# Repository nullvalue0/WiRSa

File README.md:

# RetroDisks WiRSa v3 - WiFi RS232 Serial Modem Adapter

The WiRSa v3 is a WiFi-to-RS232 serial adapter designed for legacy computing systems. It allows vintage computers to connect to modern networks via WiFi, supporting telnet BBS connectivity, file transfers, and network gateway functionality.

## Kits & assembled units available for sale
If you prefer to save yourself some time, I have some units (fully assembled or kit) available for sale. I had quite a few PCB's made up and I am trying to keep these as cheap as possible. You can purchase on [SmallRun](https://smallrun.net/shop/retrodisks/wirsa-v3-wifi-rs232-serial-modem).

## Features

### Hardware

- **Processor:** ESP-WROOM-32D with WiFi and Bluetooth 4.2 BLE
- **Display:** 128x64 two-color OLED display for settings, commands, and real-time data
- **Serial Port:** Female DB9 (DE9) connector
- **Full RS232 Breakout:**
  - DSR/DTR (Data Set Ready / Data Terminal Ready)
  - RTS/CTS (Request to Send / Clear to Send)
  - DCD (Data Carrier Detect)
  - RI (Ring Indicator)
- **Storage:** Built-in micro SD card reader for file transfers and text playback
- **Power:**
  - USB-C power connector
  - Optional 2000mAh 3.7V Li-Po battery (~14 hours runtime)
- **Navigation:** Four physical buttons for menu navigation

### Operating Modes

1. **MODEM Mode** - Hayes-compatible AT command modem emulation for telnet/BBS connectivity
2. **Telnet Server** - Built-in telnet server allows for remote terminal access
3. **File Transfer** - Binary file transfer directly from SD card via XModem, YModem, and ZModem protocols
4. **Text Playback** - Display text files from SD card through the serial port
5. **PPP Gateway** - Point-to-Point Protocol gateway for TCP/IP networking
6. **SLIP Gateway** - Serial Line Internet Protocol gateway
7. **Utilities** - Diagnostics and troubleshooting tools including signal monitoring and loopback testing
8. **Config** - Settings for baud rate, serial configuration, display orientation, and more

### Software Features

- **AT Command Set** - Full Hayes-compatible modem commands
- **Web Interface** - Built-in web server for status monitoring, configuration and file management
- **Flow Control** - Hardware (RTS/CTS) and software (XON/XOFF) flow control
- **Speed Dial** - 10 programmable speed dial entries
- **PETSCII Translation** - Support for Commodore computers
- **Telnet Protocol** - Automatic Telnet IAC handling
- **OTA Updates** - Over-the-air firmware updates via HTTP

.jpg)

## Getting Started

### WiFi Configuration

1. Connect to your computer via serial port (default: 9600 baud, 8N1)
2. Enter your WiFi credentials using AT commands (2.4 GHz networks only):
   ```
   AT$SSID=YourNetworkName
   AT$PASS=YourPassword
   ```
3. Save settings: `AT&W`
4. Reboot or reconnect to apply

### Connecting to a BBS

Use the dial command with the host and port:
```
ATDT bbs.example.com:23
```

Or configure speed dial entries:
```
AT&Z0=bbs.example.com:23
ATDS0
```

### Useful AT Commands

| Command | Description |
|---------|-------------|
| `AT` | Test connection (returns OK) |
| `ATDT<host:port>` | Dial/connect to TCP host |
| `ATDS<0-9>` | Speed dial entry |
| `ATH` | Hang up connection |
| `ATA` | Answer incoming connection |
| `ATO` | Return online from command mode |
| `+++` | Escape to command mode (during connection) |
| `ATE0/1` | Echo off/on |
| `ATV0/1` | Verbose results off/on |
| `ATI` | Display network info |
| `AT&V` | View current settings |
| `AT&W` | Save settings to EEPROM |
| `ATZ` | Load settings from EEPROM |
| `AT&F` | Restore factory defaults |
| `AT&K<0/1/2>` | Flow control (0=none, 1=hardware, 2=software) |
| `ATNET<0/1>` | Telnet protocol handling off/on |
| `ATPET=<0/1>` | PETSCII translation off/on |
| `AT$SSID=` | Set WiFi SSID |
| `AT$PASS=` | Set WiFi password |
| `AT$SP=<port>` | Set listening port |
| `ATS0=<0/1>` | Auto-answer off/on |
| `ATFC` | Check for firmware updates |
| `ATFU` | Perform firmware update |
| `AT?` or `ATHELP` | Display help |
| `ATX` | Exit MODEM Mode, return to WiRSa main menu |

## File Transfers

The WiRSa supports binary file transfers directly from the SD card using industry-standard protocols:

- **XModem** - Basic 128-byte block transfer with checksum
- **YModem** - Batch file transfer with filename and size
- **ZModem** - Streaming protocol with CRC16/CRC32 and automatic resume

To transfer files:
1. Insert SD card with files
2. Select "File Transfer" from the main menu
3. Choose the transfer protocol
4. Select send or receive
5. Initiate the transfer from your terminal software

## SLIP / PPP Gateway Modes

The WiRSa provides full TCP/IP networking capabilities for vintage computers through two standard protocols: **SLIP** (Serial Line Internet Protocol) and **PPP** (Point-to-Point Protocol). These modes turn the WiRSa into a dial-up internet gateway, allowing retro systems to browse the web, use email clients, FTP, and access other network services.

### How It Works

Both modes operate as NAT (Network Address Translation) gateways:
1. The vintage computer connects via the serial port
2. The WiRSa performs NAT translation between the serial link and WiFi
3. Outbound traffic is routed to the internet via the ESP32's WiFi connection
4. The vintage computer appears to have full internet access

### SLIP Mode

SLIP is a simpler, older protocol with less overhead. It works well with:
- **DOS** with packet drivers (ETHERSLIP, SLIPPER, etc.)
- **Early Windows 3.x** with Trumpet Winsock
- **Classic Mac OS** with MacSLIP or InterSLIP
- **Linux** with `slattach`

**Default Configuration:**
- Gateway IP: 192.168.7.1 (WiRSa)
- Client IP: 192.168.7.2 (vintage computer)
- DNS: 8.8.8.8

### PPP Mode

PPP is more robust with built-in negotiation, authentication support, and error detection. It's the standard for:
- **Windows 95/98/ME** Dial-Up Networking
- **Windows 3.11** with Microsoft DUN
- **Mac OS 8/9** with PPP/Remote Access
- **Linux** with `pppd`

**Default Configuration:**
- Gateway IP: 192.168.8.1 (WiRSa)
- Client IP: 192.168.8.2 (assigned to client)
- Primary DNS: 8.8.8.8
- Secondary DNS: 8.8.4.4

### Entering SLIP/PPP Mode

**From the WiRSa Menu: (*if your host OS is expecting an "always on" connection*)**
1. Navigate to "PPP Gateway" or "SLIP Gateway" from the main menu
2. Select "Start Gateway"

**Using AT Dial Commands: (*must set the device to Modem Mode first*)**
```
ATDT SLIP      - Enter SLIP mode
ATDT 7547      - Enter SLIP mode (phone keypad for "SLIP")

ATDT PPP       - Enter PPP mode
ATDT 777       - Enter PPP mode (phone keypad for "PPP")
```

**Using AT Commands: (*must set the device to Modem Mode first*)**
```
AT$SLIP        - Enter SLIP mode directly
AT$PPP         - Enter PPP mode directly
```

### Port Forwarding

Port forwarding allows incoming connections from the internet to reach services running on your vintage computer. This is useful for:

- **Hosting a BBS** - Run a BBS on your vintage computer accessible from the internet
- **FTP Server** - Share files from your retro machine
- **Web Server** - Host a vintage web server (Windows 95 Personal Web Server, etc.)
- **Game Servers** - Host multiplayer games on classic systems
- **SSH/Telnet Access** - Remote into your vintage computer

**Configuring Port Forwards:**

From the menu:
1. Enter SLIP or PPP Gateway menu
2. Select "Port Forwards"
3. Choose "Add Forward"
4. Enter protocol (TCP/UDP), external port, internal IP, and internal port

Using AT commands:
```
AT$SLIPFWD=TCP,80,80      - Forward TCP port 80 to client port 80
AT$SLIPFWD=UDP,53,53      - Forward UDP port 53 (DNS)
AT$SLIPFWDDEL=0           - Remove forward at index 0

AT$PPPFWD=TCP,23,23       - Forward TCP port 23 (telnet)
AT$PPPFWD=TCP,21,21       - Forward TCP port 21 (FTP)
AT$PPPFWDDEL=0            - Remove forward at index 0
```

**Note:** Port forwards are shared between SLIP and PPP modes and persist across reboots.

### Setting Up SLIP Under DOS

**Requirements:**
- MS-DOS, DR-DOS, FreeDOS, etc
- A SLIP packet driver (ETHERSLIP, SLIPPER, or CSLIPPER)
- TCP/IP applications (mTCP suite, Arachne or MicroWeb browser, NCSA Telnet, etc.)

**Step 1: Configure WiRSa**
```
AT$SSID=YourWiFiNetwork
AT$PASS=YourPassword
AT&W
```

**Step 2: Install Packet Driver**

Create a batch file (e.g., `SLIP.BAT`):
```batch
@echo off
REM Load SLIP packet driver on COM1 at 115200 baud
ETHERSL 0x60 4 0x3F8 115200
REM Or for COM2: ETHERSL 0x60 3 0x2F8 115200
```

**Step 3: Configure TCP/IP Stack**

For mTCP, create `MTCP.CFG`:
```
PACKETINT 0x60
IPADDR 192.168.7.2
NETMASK 255.255.255.0
GATEWAY 192.168.7.1
NAMESERVER 8.8.8.8
```

Set environment variable:
```batch
SET MTCPCFG=C:\MTCP\MTCP.CFG
```

**Step 4: Connect**

On the WiRSa, start SLIP Gateway by enabling from the buttons/screen menu, from the serial menu (exit terminal after Starting Gateway, it starts immediately), or by dialing
```
ATDT SLIP
```

**Step 5: Test Connection**
```
PING 8.8.8.8
TELNET bbs.example.com
```

### Setting Up PPP Under Windows 95/98 Dial-Up Networking

**Step 1: Create a New Connection**
1. Open "My Computer" → "Dial-Up Networking"
2. Click "Make New Connection"
3. Name it "WiRSa Internet" (or any name)
4. Select your serial port modem (or "Standard Modem" on the COM port)
5. For phone number, enter: `PPP` (or `777`)

**Step 2: Configure the Connection**
1. Right-click the new connection → "Properties"
2. **General tab:** Ensure correct modem/port is selected
3. **Server Types tab:**
   - Type of Dial-Up Server: "PPP: Internet, Windows NT Server, Windows 98"
   - Uncheck "Log on to network" (unless needed)
   - Check "Enable software compression" (optional)
   - Check "TCP/IP" under Allowed network protocols
   - Uncheck NetBEUI and IPX/SPX unless needed
4. Click "TCP/IP Settings":
   - Select "Server assigned IP address"
   - Select "Server assigned name server addresses"
   - Click OK

**Step 3: Modem Settings**
1. Go to Control Panel → Modems → Properties
2. Set maximum speed to match WiRSa baud rate (115200 recommended, plus Flow Control enabled [AT&K1])
3. Under "Connection" tab, set 8 data bits, No parity, 1 stop bit
4. Make sure to put the WiRSa into Modem mode before proceeding

**Step 4: Connect**
1. Double-click the connection
2. Leave username/password blank (or enter any values - WiRSa ignores auth)
3. Click "Connect"
4. The WiRSa will respond "CONNECT PPP" and negotiate the link

**Step 5: Verify Connection**
- Open a command prompt: `ping 8.8.8.8`
- Open Internet Explorer and browse!

### Setting Up PPP Under Windows 3.11

**Requirements:**
- Windows 3.11 for Workgroups
- Microsoft TCP/IP-32 or Trumpet Winsock
- Dial-Up Networking 1.0 for Windows 3.11

**Step 1: Install TCP/IP-32**
1. Run Network Setup
2. Add "Microsoft TCP/IP-32"
3. Configure with DHCP or manual IP (the WiRSa will assign IPs)

**Step 2: Configure RAS (Remote Access Service)**
1. Install RAS if not present
2. Add your modem on the appropriate COM port
3. Create a new phonebook entry with phone number "PPP" or "777"

**Step 3: Connect**
1. Open Remote Access
2. Select your WiRSa entry
3. Make sure WiRSa is in Modem Mode
4. Click "Dial"

### Setting Up SLIP Under Linux

Linux has built-in SLIP support via the `slattach` utility. This guide covers configuring the serial port, enabling SLIP, and testing connectivity.

**Requirements:**
- Linux system with a physical serial port (directly connected to WiRSa)
- Root/sudo access
- `slattach` utility (usually included in `net-tools` or `slip` package)

**Step 1: Identify Your Serial Port**

First, identify the serial device. Physical serial ports are typically:
```bash
# First serial port (COM1 equivalent)
/dev/ttyS0

# Second serial port (COM2 equivalent)
/dev/ttyS1

# List available serial ports
ls -la /dev/ttyS*

# Check which serial ports are available
dmesg | grep -i ttyS
```

**Step 2: Configure the Serial Port**

Before starting SLIP, configure the serial port to match your WiRSa settings. Use `stty` to set the baud rate and other parameters:

```bash
# Set baud rate to 115200, 8N1, no flow control
sudo stty -F /dev/ttyS0 115200 cs8 -cstopb -parenb raw -echo

# For hardware flow control (if WiRSa has AT&K1 enabled), add crtscts:
sudo stty -F /dev/ttyS0 115200 cs8 -cstopb -parenb raw -echo crtscts

# Verify settings
stty -F /dev/ttyS0 -a
```

Key `stty` options:
| Option | Description |
|--------|-------------|
| `115200` | Baud rate (match WiRSa setting) |
| `cs8` | 8 data bits |
| `-cstopb` | 1 stop bit (use `cstopb` for 2) |
| `-parenb` | No parity |
| `raw` | Raw mode (no input/output processing) |
| `-echo` | Disable local echo |
| `crtscts` | Enable hardware flow control |

**Step 3: Test Serial Communication**

Before enabling SLIP, verify you can communicate with the WiRSa:

```bash
# Open a simple terminal session
# Press Ctrl+C to exit when done
sudo cat /dev/ttyS0 &
echo "AT" | sudo tee /dev/ttyS0

# You should see "OK" response from WiRSa
# Kill the background cat process
kill %1

# Alternative: use screen or minicom
screen /dev/ttyS0 115200
# (Press Ctrl+A then K to exit screen)
```

**Step 4: Start SLIP Gateway on WiRSa**

From your terminal session with WiRSa, enter SLIP mode:
```
AT$SLIP
```
Or dial into SLIP mode:
```
ATDT SLIP
```

You should see "CONNECT SLIP" response. Now exit your terminal program (the serial port must be free for slattach).

**Step 5: Enable SLIP on Linux**

Attach the SLIP interface using `slattach`:

```bash
# Start slattach in the background
# -p slip = SLIP protocol
# -s 115200 = baud rate
sudo slattach -p slip -s 115200 /dev/ttyS0 &

# Note the PID for later cleanup
SLATTACH_PID=$!
```

**Step 6: Configure the Network Interface**

Once slattach is running, a `sl0` interface will be created. Configure it:

```bash
# Bring up the interface with the client IP
sudo ifconfig sl0 192.168.7.2 pointopoint 192.168.7.1 up

# Or using ip command (modern systems)
sudo ip addr add 192.168.7.2 peer 192.168.7.1 dev sl0
sudo ip link set sl0 up

# Add default route through the SLIP gateway (optional - routes all traffic through WiRSa)
sudo ip route add default via 192.168.7.1 dev sl0

# Or add only specific routes
sudo ip route add 8.8.8.8 via 192.168.7.1 dev sl0
```

**Step 7: Configure DNS**

Add the DNS server to your resolver configuration:

```bash
# Temporary - add to /etc/resolv.conf
echo "nameserver 8.8.8.8" | sudo tee -a /etc/resolv.conf

# For systems using systemd-resolved
sudo resolvectl dns sl0 8.8.8.8
```

**Step 8: Test the Connection**

Verify connectivity through the SLIP link:

```bash
# Ping the WiRSa gateway
ping -c 3 192.168.7.1

# Ping an external IP (Google DNS)
ping -c 3 8.8.8.8

# Test DNS resolution
ping -c 3 google.com

# Check routing
ip route show
```

Expected output for successful ping:
```
PING 192.168.7.1 (192.168.7.1) 56(84) bytes of data.
64 bytes from 192.168.7.1: icmp_seq=1 ttl=64 time=5.23 ms
64 bytes from 192.168.7.1: icmp_seq=2 ttl=64 time=4.89 ms
64 bytes from 192.168.7.1: icmp_seq=3 ttl=64 time=5.01 ms
```

**Step 9: Cleanup (When Done)**

To disconnect and clean up:

```bash
# Bring down the interface
sudo ip link set sl0 down

# Kill slattach
sudo kill $SLATTACH_PID
# Or find and kill by name
sudo killall slattach
```

**Complete Setup Script**

Here's a complete script to automate the Linux SLIP setup:

```bash
#!/bin/bash
# slip-connect.sh - Connect to WiRSa via SLIP

DEVICE="/dev/ttyS0"
BAUD="115200"
LOCAL_IP="192.168.7.2"
GATEWAY_IP="192.168.7.1"
DNS="8.8.8.8"

# Configure serial port
sudo stty -F $DEVICE $BAUD cs8 -cstopb -parenb raw -echo

# Start slattach
sudo slattach -p slip -s $BAUD $DEVICE &
sleep 2

# Configure interface
sudo ip addr add $LOCAL_IP peer $GATEWAY_IP dev sl0
sudo ip link set sl0 up

# Add route for external traffic
sudo ip route add default via $GATEWAY_IP dev sl0

# Configure DNS
sudo resolvectl dns sl0 $DNS 2>/dev/null || echo "nameserver $DNS" | sudo tee /etc/resolv.conf

echo "SLIP connection established"
echo "  Local IP:  $LOCAL_IP"
echo "  Gateway:   $GATEWAY_IP"
echo "  DNS:       $DNS"
echo ""
echo "Test with: ping 8.8.8.8"
```

**Troubleshooting**

| Issue | Solution |
|-------|----------|
| "Device or resource busy" | Another program is using the serial port. Close any terminal emulators. |
| No sl0 interface appears | Check if slattach is running: `ps aux \| grep slattach`. Verify WiRSa is in SLIP mode. |
| Ping to gateway fails | Verify serial settings match WiRSa. Check cable connections. |
| External pings fail | Ensure WiRSa has WiFi connectivity. Check `AT$SLIPSTAT` for packet statistics. |
| Permission denied | Use sudo or add your user to the `dialout` group: `sudo usermod -aG dialout $USER` |
| Serial port not found | Ensure the serial port is enabled in BIOS/UEFI. Check `setserial -g /dev/ttyS*` for port status. |

### Configuration AT Commands

**SLIP Configuration:**
| Command | Description |
|---------|-------------|
| `AT$SLIP` | Enter SLIP gateway mode |
| `AT$SLIPIP=x.x.x.x` | Set gateway IP address |
| `AT$SLIPCLIENT=x.x.x.x` | Set client IP address |
| `AT$SLIPDNS=x.x.x.x` | Set DNS server |
| `AT$SLIPSHOW` | Show current SLIP configuration |
| `AT$SLIPSTAT` | Show SLIP statistics |
| `AT$SLIPFWD=proto,ext,int` | Add port forward |
| `AT$SLIPFWDDEL=index` | Remove port forward |

**PPP Configuration:**
| Command | Description |
|---------|-------------|
| `AT$PPP` | Enter PPP gateway mode |
| `AT$PPPGW=x.x.x.x` | Set gateway IP address |
| `AT$PPPPOOL=x.x.x.x` | Set client pool start IP |
| `AT$PPPDNS=x.x.x.x` | Set primary DNS server |
| `AT$PPPDNS2=x.x.x.x` | Set secondary DNS server |
| `AT$PPPSHOW` | Show current PPP configuration |
| `AT$PPPSTAT` | Show PPP statistics |
| `AT$PPPFWD=proto,ext,int` | Add port forward |
| `AT$PPPFWDDEL=index` | Remove port forward |
| `AT$PPPFWDLIST` | List all port forwards |

### Exiting SLIP/PPP Mode

- Press the **BACK button** on the WiRSa
- Send `+++` escape sequence (USB serial only in SLIP mode)
- Disconnect from the client side (PPP will detect link termination)

## Telnet Server Mode

The WiRSa includes a built-in Telnet server that allows remote access to devices connected via the serial port. This is useful for:

- **Vintage terminals and computers** - Access systems that originally connected to serial terminals (mainframes, minicomputers, Unix systems)
- **Serial console access** - Remotely manage routers, switches, or embedded devices with serial management ports
- **Headless systems** - Access single-board computers or systems without displays
- **BBS hosting** - Run a BBS on a vintage computer and accept telnet connections

### How It Works

1. The WiRSa listens for incoming TCP connections on a configurable port (default: 23)
2. When a connection is made, data is bridged bidirectionally between the telnet client and the serial port
3. The remote user interacts with whatever is connected to the WiRSa's serial port as if they were locally connected

### Configuration

**Set the listening port:**
```
AT$SP=23        - Set server port to 23 (default telnet port)
AT$SP=2323      - Use alternate port 2323
AT$SP?          - Query current port
```

**Configure auto-answer:**
```
ATS0=1          - Enable auto-answer (automatically connect incoming calls)
ATS0=0          - Disable auto-answer (ring and wait for manual answer)
ATS0?           - Query current setting
```

**Telnet protocol handling:**
```
ATNET1          - Enable telnet IAC sequence handling (recommended for telnet clients)
ATNET0          - Disable telnet handling (raw TCP mode)
ATNET?          - Query current setting
```

### Connecting to the WiRSa

From any computer on the same network:
```bash
telnet <wirsa-ip-address> 23
```

Or with a custom port:
```bash
telnet <wirsa-ip-address> 2323
```

### Console Mode vs Call Mode

The WiRSa supports two types of incoming connections:

**Console Connection (First Connection):**
- The first telnet connection becomes a "console" session
- Stays in AT command mode - you can type AT commands
- Use `ATDT <host:port>` to dial out to BBSes
- Full modem emulation available

**Call Connection (With Auto-Answer):**
- When `ATS0=1` is set, subsequent connections bridge directly to serial
- Data passes transparently between telnet and serial
- Use `+++` to escape back to command mode
- Use `ATH` to hang up

### Example: Remote Terminal Access

**Scenario:** You have a vintage Unix system with a serial console, and you want to access it remotely via telnet.

1. Connect the WiRSa to the Unix system's serial port
2. Configure WiRSa to match the system's serial settings:
   ```
   AT$SB=9600      - Set baud rate (match your system)
   ATS0=1          - Enable auto-answer
   ATNET1          - Enable telnet handling
   AT&W            - Save settings
   ```
3. From a remote computer, telnet to the WiRSa's IP address
4. You'll be connected directly to the Unix system's serial console

### Example: Hosting a BBS

**Scenario:** Run a BBS on a vintage computer and accept incoming telnet connections.

1. Connect WiRSa to the vintage computer running BBS software
2. Configure WiRSa:
   ```
   AT$SP=23        - Listen on port 23
   ATS0=1          - Auto-answer incoming connections
   ATNET1          - Handle telnet protocol
   AT&W            - Save settings
   ```
3. Configure your router to forward port 23 to the WiRSa's IP address
4. Users can now telnet to your public IP to access the BBS

### Manual Answer Mode

When auto-answer is disabled (`ATS0=0`), incoming connections trigger a "RING" message:

```
RING
RING
RING
```

To answer manually, type:
```
ATA             - Answer the incoming call
```

This is useful when you want to screen incoming connections or when the connected device needs preparation before accepting a connection.

## Diagnostics

The Utilities menu provides diagnostic tools for troubleshooting:

- **Signal Monitor** - Real-time display of RS232 signal states (DCD, RTS, CTS, DTR, DSR, RI)
- **Loopback Test** - Test serial communication integrity
- **Statistics** - View connection counts and byte transfer statistics

## Hardware Connections

### Pin Assignments

| Function | GPIO | Description |
|----------|------|-------------|
| RXD2 | 16 | UART2 RX (from computer) |
| TXD2 | 17 | UART2 TX (to computer) |
| DCD | 33 | Data Carrier Detect (output) |
| RTS | 15 | Request to Send (output) |
| CTS | 27 | Clear to Send (input) |
| DTR | 4 | Data Terminal Ready |
| DSR | 26 | Data Set Ready |
| RI | 25 | Ring Indicator |
| SD CS | 5 | SD Card Chip Select |
| SD MOSI | 23 | SD Card MOSI |
| SD MISO | 19 | SD Card MISO |
| SD SCK | 18 | SD Card Clock |

### Navigation Buttons

| Button | GPIO | Function |
|--------|------|----------|
| SW1 | 36 | DOWN |
| SW2 | 39 | BACK |
| SW3 | 34 | ENTER |
| SW4 | 35 | UP |

## Building the Firmware

This is a PlatformIO project. See [README-PLATFORMIO.md](README-PLATFORMIO.md) for detailed build instructions.

Quick start:
```bash
# Build firmware
platformio run

# Upload to ESP32
platformio run --target upload

# Monitor serial output
platformio device monitor
```

## Origin Story

The WiRSa originated as a film prop for Apple TV's "The Shining Girls," where it simulated realistic computer interaction by playing back pre-recorded text files while actors typed on vintage terminals.

## Resources

- **Source Code:** Complete firmware, schematics (KiCAD), Gerber files, and enclosure designs (OpenSCAD) available in this repository
- **Contact:** nullvalue@gmail.com

## License

MIT License - See source code header for full license text.

Copyright (C) 2026 Aron Hoekstra

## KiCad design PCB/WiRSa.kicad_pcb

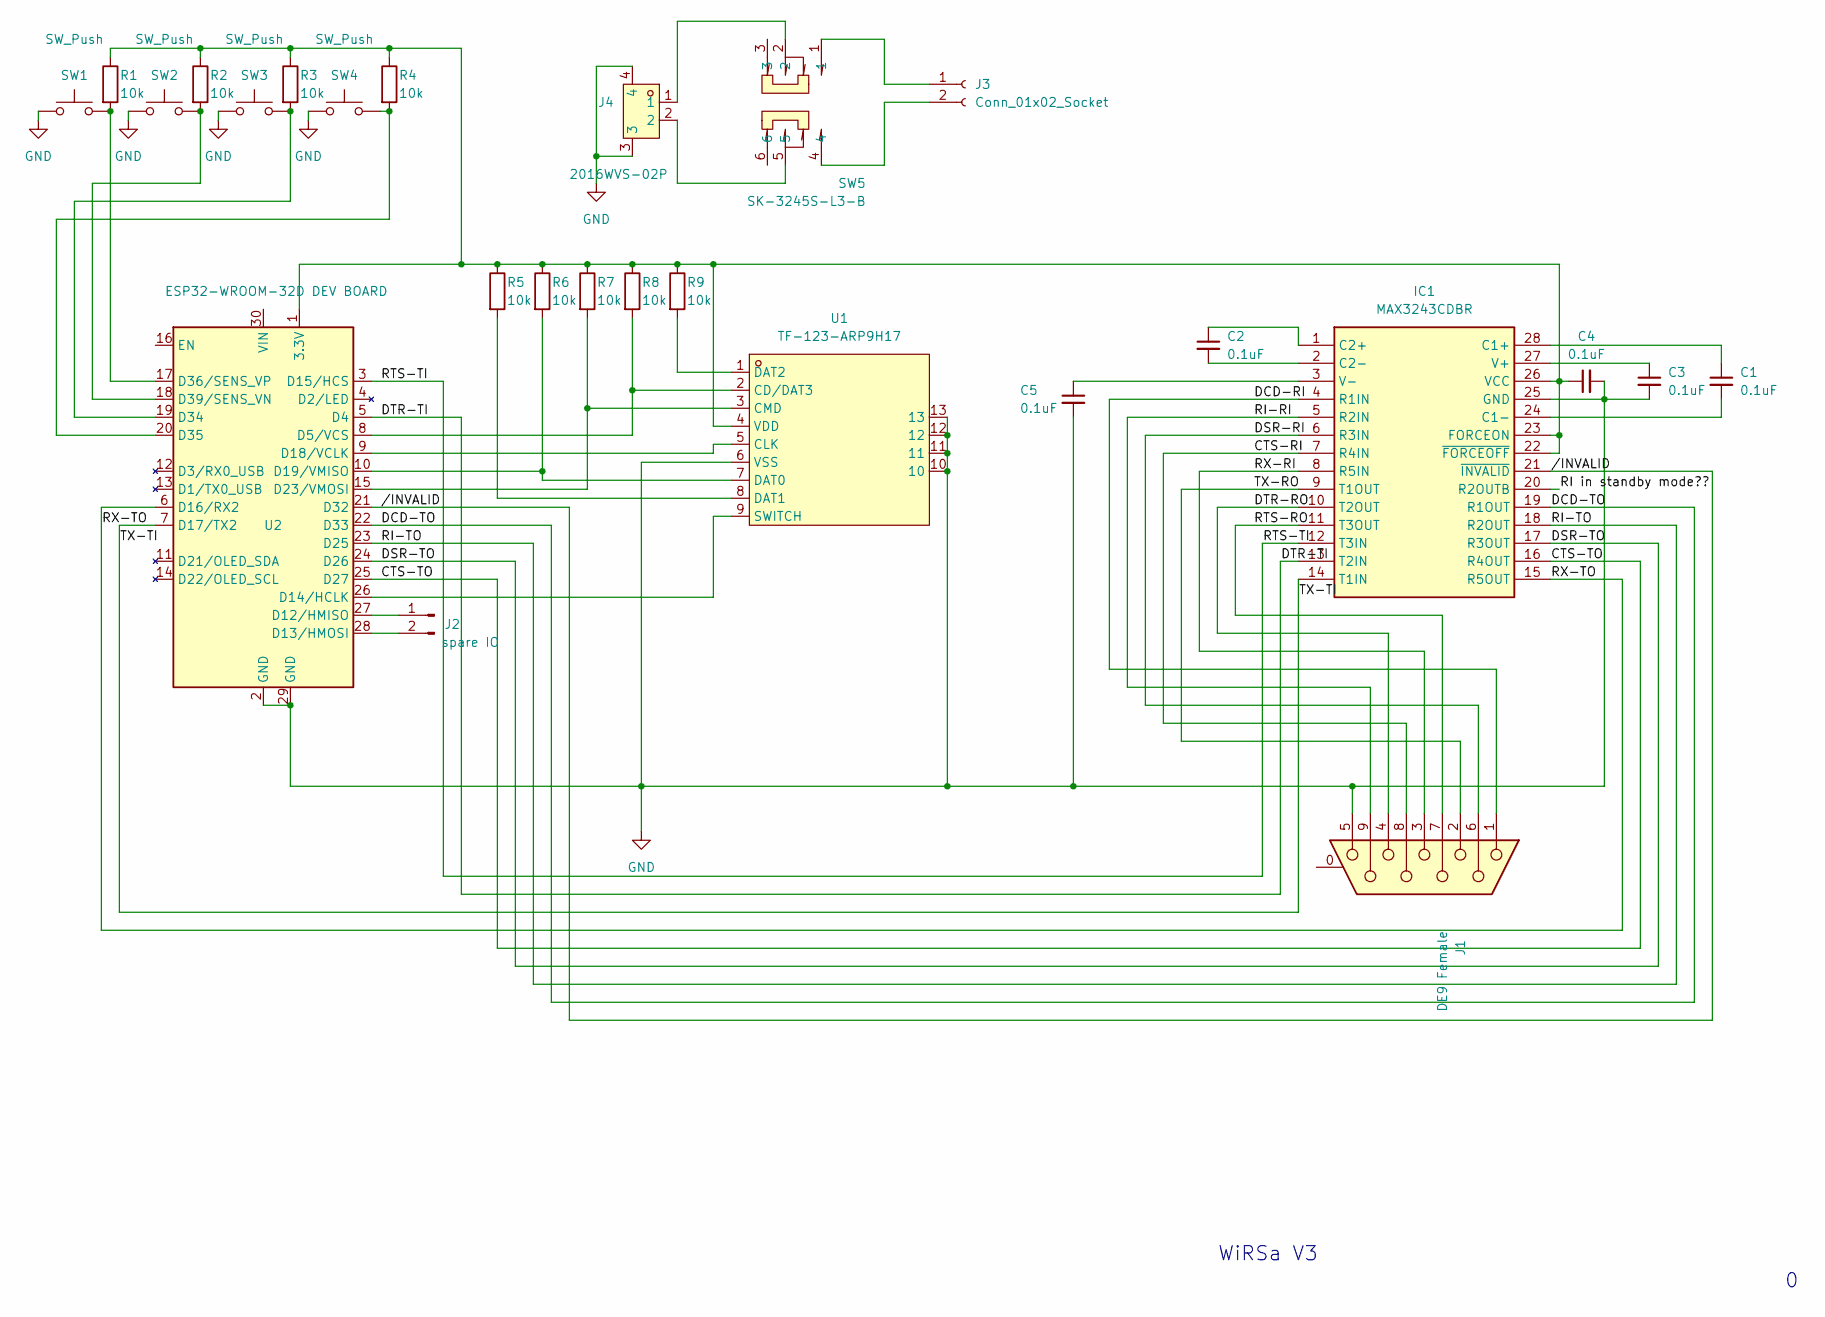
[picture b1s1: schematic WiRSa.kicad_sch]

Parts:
C1, C2, C3, C4, C5: 0.1uF; C_0603_1608Metric; LCSC C14663
IC1: MAX3243CDBR; SSOP-28_L10.2-W5.3-P0.65-LS7.8-BL; LCSC Part C414614
J1: DE9 Female; DSUB-9_Female_Horizontal_P2.77x2.84mm_EdgePinOffset4.94mm_H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
J2: spare IO; PinHeader_1x02_P2.54mm_Vertical
J3: Conn_01x02_Socket; PinHeader_1x02_P2.54mm_Vertical
J4: 2016WVS-02P; CONN-SMD_P2.00_X2016WVS-02-9TSW; LCSC Part C5448068
R1, R2, R3, R4, R5, R6, R7, R8, R9: 10k; R_0603_1608Metric; LCSC C25804
SW1, SW2, SW3, SW4: SW_Push; SW_Tactile_SPST_Angled_PTS645Vx58-2LFS
SW5: SK-3245S-L3-B; SW-SMD_SK-3245S-L3-B; LCSC Part C405954
U1: TF-123-ARP9H17; TF-SMD_TF-123-ARP9H15; LCSC Part C2982548
U2: ESP32-WROOM-32D DEV BOARD; ESP32-C3-DevKitC-02

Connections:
/CTS-RI: IC1.7 (R4IN), J1.8
/CTS-TO: IC1.16 (R4OUT), U2.25 (D27)
/DCD-RI: IC1.4 (R1IN), J1.1
/DCD-TO: IC1.19 (R1OUT), U2.22 (D33)
/DSR-RI: IC1.6 (R3IN), J1.6
/DSR-TO: IC1.17 (R3OUT), U2.24 (D26)
/DTR-RO: IC1.10 (T2OUT), J1.4
/DTR-TI: IC1.13 (T2IN), U2.5 (D4)
/RI in standby mode??: IC1.20 (R2OUTB)
/RI-RI: IC1.5 (R2IN), J1.9
/RI-TO: IC1.18 (R2OUT), U2.23 (D25)
/RTS-RO: IC1.11 (T3OUT), J1.7
/RTS-TI: IC1.12 (T3IN), U2.3 (D15/HCS)
/RX-RI: IC1.8 (R5IN), J1.3
/RX-TO: IC1.15 (R5OUT), U2.6 (D16/RX2)
/TX-RO: IC1.9 (T1OUT), J1.2
/TX-TI: IC1.14 (T1IN), U2.7 (D17/TX2)
//INVALID: IC1.21 (~INVALID), U2.21 (D32)
GND: C3.2, C4.2, C5.2, IC1.25 (GND), J1.5, J4.3, J4.4, SW1.1, SW2.1, SW3.1, SW4.1, U1.6 (VSS), U1.10, U1.11, U1.12, U1.13, U2.2 (GND), U2.29 (GND)
unnamed: C1.1, IC1.28 (C1+)
unnamed: C1.2, IC1.24 (C1-)
unnamed: C2.1, IC1.1 (C2+)
unnamed: C2.2, IC1.2 (C2-)
unnamed: C4.1, IC1.22 (~FORCEOFF), IC1.23 (FORCEON), IC1.26 (VCC), R1.1, R2.1, R3.1, R4.1, R5.1, R6.1, R7.1, R8.1, R9.1, U1.4 (VDD), U2.1 (3.3V)
unnamed: C3.1, IC1.27 (V+)
unnamed: C5.1, IC1.3 (V-)
unnamed: J2.1, U2.27 (D12/HMISO)
unnamed: J2.2, U2.28 (D13/HMOSI)
unnamed: J3.1, SW5.1
unnamed: J3.2, SW5.4
unnamed: J4.1, SW5.2
unnamed: J4.2, SW5.5
unnamed: R8.2, U1.2 (CD/DAT3), U2.8 (D5/VCS)
unnamed: U1.5 (CLK), U2.9 (D18/VCLK)
unnamed: R7.2, U1.3 (CMD), U2.15 (D23/VMOSI)
unnamed: R6.2, U1.7 (DAT0), U2.10 (D19/VMISO)
unnamed: R5.2, U1.8 (DAT1)
unnamed: R9.2, U1.1 (DAT2)
unnamed: U1.9 (SWITCH), U2.26 (D14/HCLK)
unnamed: R3.2, SW3.2, U2.19 (D34)
unnamed: R4.2, SW4.2, U2.20 (D35)
unnamed: R1.2, SW1.2, U2.17 (D36/SENS_VP)
unnamed: R2.2, SW2.2, U2.18 (D39/SENS_VN)

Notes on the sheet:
WiRSa V3

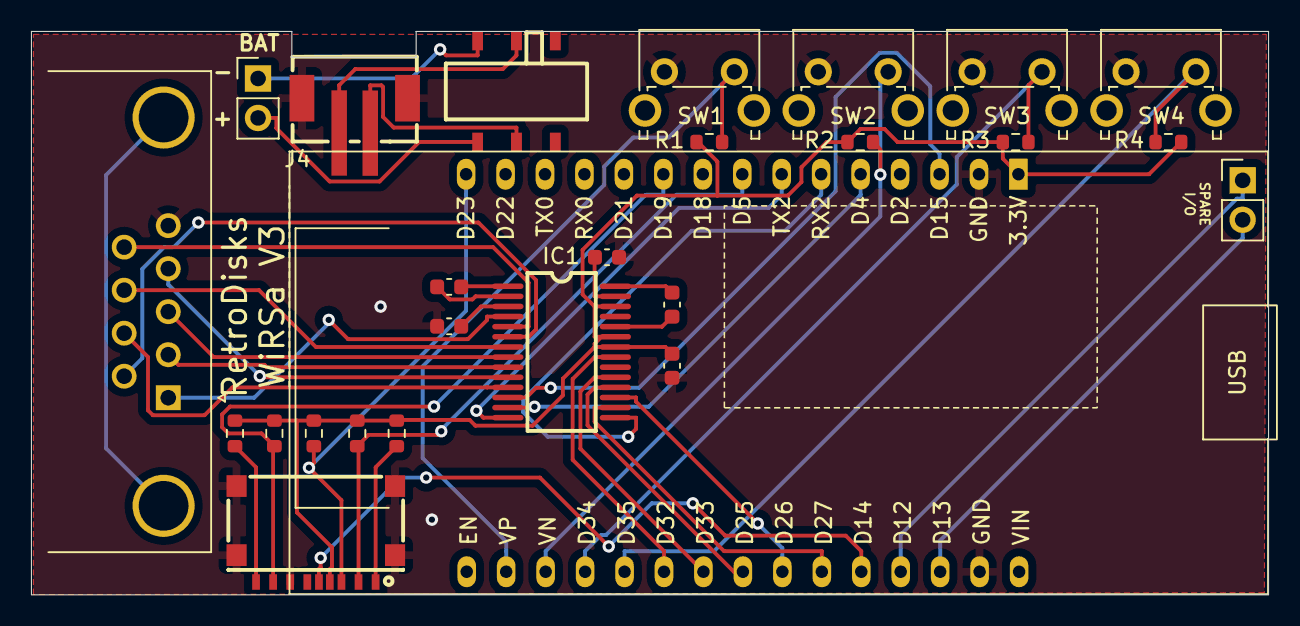
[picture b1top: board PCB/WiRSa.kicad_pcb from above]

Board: 2 copper layers, 79.6 x 36.3 mm, 26 parts (0 on the bottom side), 42 nets.

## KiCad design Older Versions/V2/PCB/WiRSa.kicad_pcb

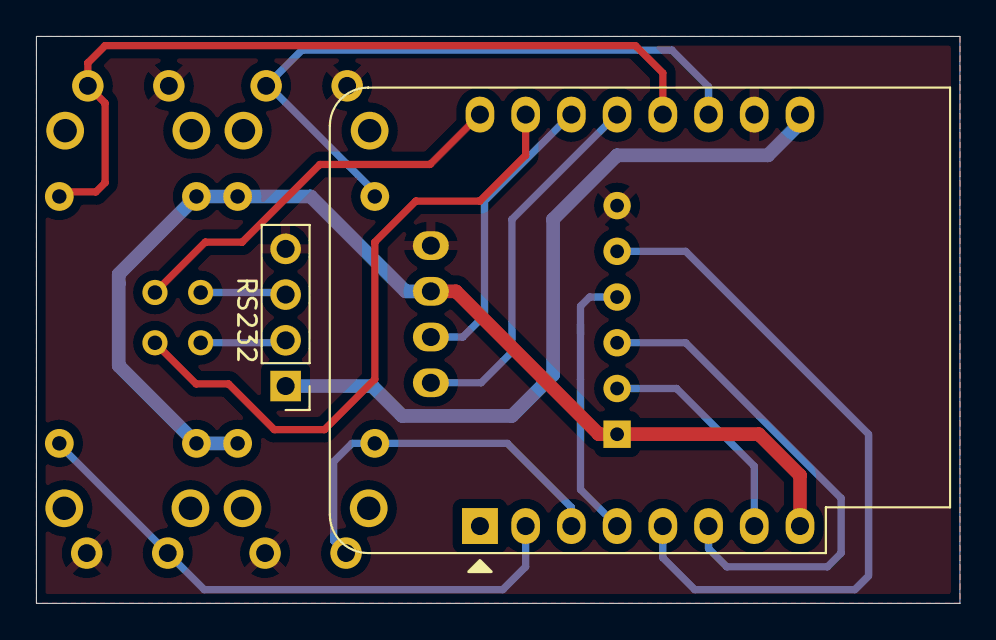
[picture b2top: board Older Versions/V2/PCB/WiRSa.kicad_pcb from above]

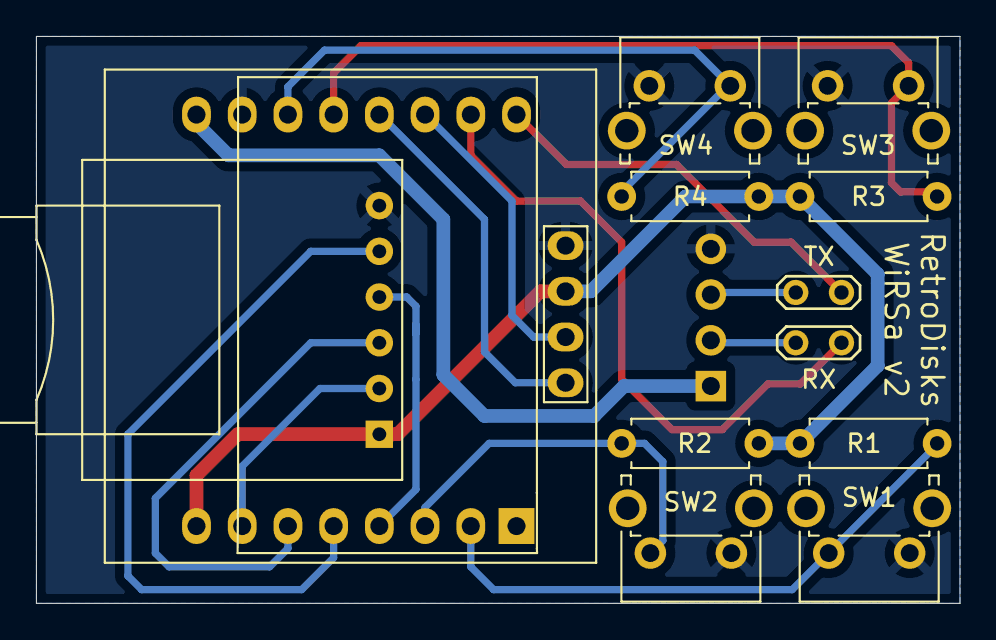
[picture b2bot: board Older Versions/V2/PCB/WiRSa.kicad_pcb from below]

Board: 2 copper layers, 51.3 x 31.5 mm, 14 parts (12 on the bottom side), 17 nets.

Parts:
A1: SD_Card_Module
Brd1: SSD1306; 128x64OLED
R1, R2, R3, R4: 10k; R_Axial_DIN0207_L6.3mm_D2.5mm_P7.62mm_Horizontal
RS232: RS232_TTL_Adapter; PinHeader_1x04_P2.54mm_Vertical
RX: RX; TestPoint_2Pads_Pitch2.54mm_Drill0.8mm
SW1, SW2, SW3, SW4: SW_Push; SW_Tactile_SPST_Angled_PTS645Vx58-2LFS
TX: TX; TestPoint_2Pads_Pitch2.54mm_Drill0.8mm
U1: WeMos_D1_mini; WEMOS_D1_mini_light

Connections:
GND: A1.6 (GND), Brd1.1 (GND), RS232.4 (GND), SW1.1, SW2.1, SW3.1, SW4.1, U1.10 (GND)
unnamed: A1.1 (3V3), Brd1.2 (VCC), R1.1, R2.1, R3.1, R4.1, U1.8 (3V3)
unnamed: A1.2 (CS), U1.7 (CS/D8)
unnamed: A1.3 (MOSI), U1.6 (MOSI/D7)
unnamed: A1.4 (CLK), U1.4 (SCK/D5)
unnamed: A1.5 (MISO), U1.5 (MISO/D6)
unnamed: Brd1.3 (SCL), U1.14 (SCL/D1)
unnamed: Brd1.4 (SDA), U1.13 (SDA/D2)
unnamed: RS232.1 (VCC), U1.9 (5V)
unnamed: RS232.2 (RXD), RX.1 (A)
unnamed: RS232.3 (TXD), TX.1 (A)
unnamed: RX.2 (B), U1.15 (RX)
unnamed: TX.2 (B), U1.16 (TX)
unnamed: R1.2, SW1.2, U1.2 (A0)
unnamed: R2.2, SW2.2, U1.3 (D0)
unnamed: R3.2, SW3.2, U1.12 (D3)
unnamed: R4.2, SW4.2, U1.11 (D4)

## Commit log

2022-06-27 Add kit assembly instructions
2022-08-29 new text playback features
    support for embedding VT escape commands, delays, wait for key
2022-11-01 v2 enclosure update
    Updated enclosure includes display opening on cover and openings for buttons
2022-11-01 v2 firmware update
2022-11-01 v2 PCB update
2022-11-01 v2 assembly instructions update
2022-11-01 pictures of the v2 revision assembly & enclosure
2022-11-01 v2 update notes
2022-11-02 menu improvements
2022-11-04 more menu improvements
2022-11-05 more menu fixes
2022-11-05 even more menu improvements
2022-11-05 commit test
2022-11-05 just some housekeeping
2022-11-05 new readme pictures
2022-11-12 v2.02 added default mode menu
2022-11-14 stubbed out rest of the future file transfer protocols, added XMODEM send support
2022-11-14 stubbed out future file transfer protocols, added XMODEM send support
2022-11-16 finished XMODEM implementation - send & receive
2022-11-19 improved display and menus for file transfers
2022-11-25 improved responsiveness due to display delays
2022-12-04 added WiRSa firmware version check after wifi connects
2022-12-08 Added OTA firmware update support
2023-01-23 Update README.md
    added a Getting Started section
2023-07-29 some improvements to enclosure
    Thicker walls, a slightly taller and some small adjustments to the cover to make it easier get on and slide. Overall the PCB fits better now and the enclosure should be more durable.
2023-09-17 v2.10 - Improved MODEM mode screen
    modem mode will now show wifi/call status icons, ip address, and byte count sent/recv'd
2023-09-18 Added Serial Config menu
    User can now change serial bit data bits, parity bit, and stop bit settings from the Settings menu
2023-11-11 Increases height of enclosure slightly
2024-12-09 WiRSa v3.01
    Initial push for the version 3 design
2024-12-23 add kit instructions
2024-12-29 V3 Enclosure
2024-12-29 V3 Pictures
2025-01-02 WiRSa v3.02
    Fixed reboot function for ESP32 device
2025-01-22 V3 R1
2026-01-08 WiRSa v3.03
    - refactored code, using platform.io now instead of Arduino IDE
    - fixed SD card R/W issue
    - fixed IP display (ATI etc)
    - added ZModem support
    - fix OTA update
2026-01-08 Add 3.03 firmware .bin file
2026-01-23 WiRSa v3.04
    added PPP mode
2026-01-26 Revise README for WiRSa v3 with detailed features
    Expanded the README to include detailed features, usage instructions, and hardware specifications for the WiRSa v3.
2026-01-26 Revise README for WiRSa v3
    Updated project description to clarify functionality and features.
2026-01-27 WiRSa v3.05
    added SLIP mode, improved web config interface
2026-01-27 Update README
    Added details about PPP and SLIP gateway modes, including activation methods and configuration settings.
2026-01-27 Update README
    Clarified the SLIP/PPP Gateway modes description and added emphasis on activation methods.
2026-01-31 WiRSa v3.06
    added port forwarding to SLIP/PPP modes
2026-01-31 WiRSa v3.06
2026-02-10 WiRSa v3.07
    SLIP/PPP modes bug fixes for linux compatibility (slattach, pppd)
2026-02-17 WiRSa v3.08
    - fixed wifi password entry via screen/buttons
    - implemented AT&D0-3 (DTR control)
    - DSR and RI pins now driven as outputs per RS-232 standard
2026-02-19 WiRSa v3.09
    - when S0=1 (auto-answer) telnet goes to RING/CONNECT/DCD
    - added ATQ0/ATQ1 and ATS2=N commands
2026-02-20 enclosure fix
    - fixed the reversed up/down arrows
    - added some individual STLs for printing individual parts
2026-02-21 WiRSa v3.10
    - modified signal monitor to show on screen while in modem mode
    - fixed telnet call mode to assert DCD
    - fixed some pin polarity issues
2026-04-25 Update README for SLIP/PPP mode instructions
    Clarify instructions for entering SLIP/PPP mode and modem settings.
2026-04-28 README.md
2026-05-22 Update purchase link from Tindie to SmallRun
2026-06-18 Enhance README with product badges and links
    Added badges for product availability and links to SmallRun.

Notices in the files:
README.md:
License:
MIT License - See source code header for full license text.
Copyright (C) 2026 Aron Hoekstra
